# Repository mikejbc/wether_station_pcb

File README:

# Schemat Stacji Pogodowej wraz z projektem płytki PCB

Cechy projektu:

+ Oparty na mikrokontrolerze Atmega328
+ Wykorzystuje Czujnik temperatury i wilgotności DHT 22
+ ...

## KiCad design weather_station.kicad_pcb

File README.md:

# Schemat Stacji Pogodowej wraz z projektem płytki PCB

Cechy projektu:

+ Wykonany w Kicad
+ Oparty na mikrokontrolerze Atmega328
+ Wykorzystuje Czujnik temperatury i wilgotności DHT 22
+ ...

## Źródła:

+ https://howtomechatronics.com/tutorials/arduino/arduino-wireless-weather-station-project/

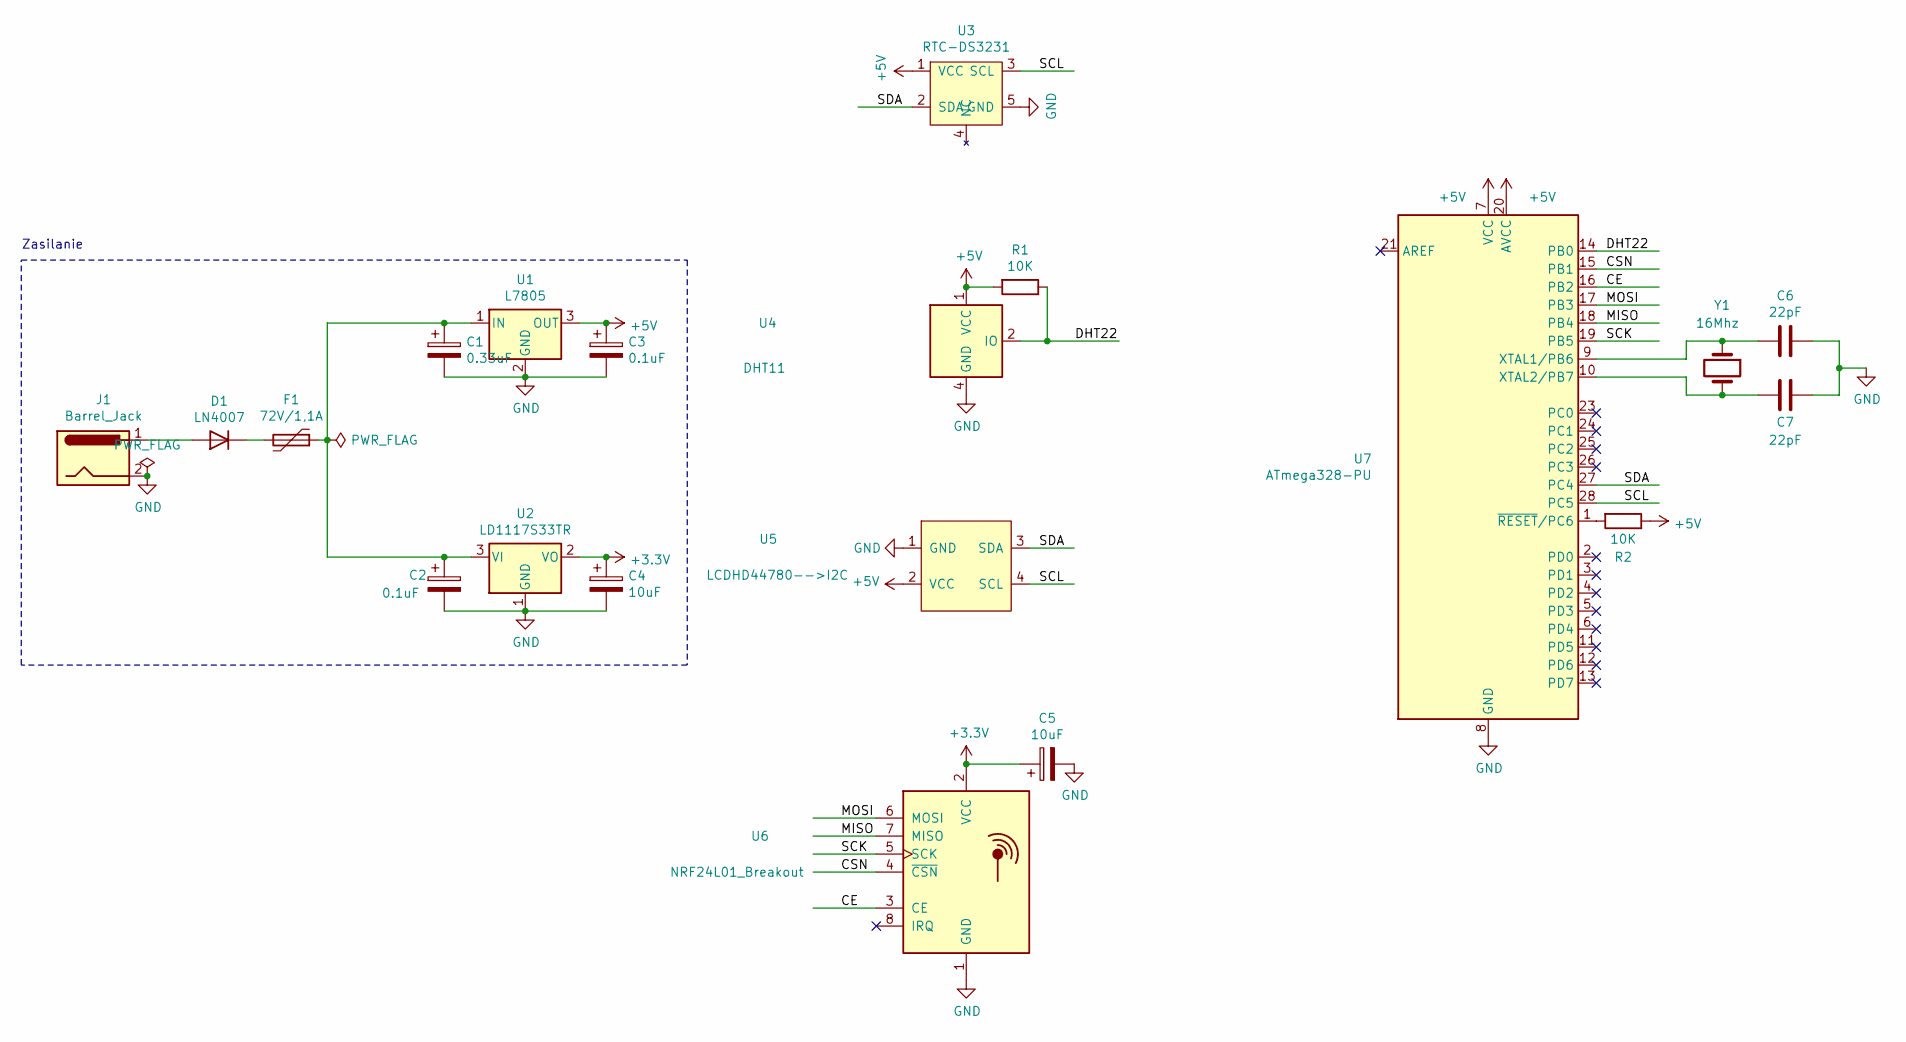
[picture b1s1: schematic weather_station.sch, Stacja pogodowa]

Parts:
C1: 0.33uF; CP_Radial_D5.0mm_P2.00mm
C2, C3: 0.1uF; CP_Radial_D5.0mm_P2.00mm
C4, C5: 10uF; CP_Radial_D5.0mm_P2.00mm
C6, C7: 22pF; C_Disc_D3.0mm_W1.6mm_P2.50mm
D1: LN4007; D_DO-41_SOD81_P10.16mm_Horizontal
F1: 72V/1,1A; Fuse_BelFuse_0ZRE0016FF_L9.9mm_W3.8mm
J1: Barrel_Jack; BarrelJack_Horizontal
R1, R2: 10K; R_Axial_DIN0207_L6.3mm_D2.5mm_P10.16mm_Horizontal
U1: L7805; TO-220-3_Vertical
U2: LD1117S33TR; TO-220-3_Vertical
U3: RTC-DS3231; PinHeader_1x05_P2.54mm_Vertical
U4: DHT11; Aosong_DHT11_5.5x12.0_P2.54mm
U5: LCDHD44780-->I2C; PinHeader_1x04_P2.54mm_Vertical
U6: NRF24L01_Breakout; NRF24-horizontal-pin-socket
U7: ATmega328-PU; DIP-28_W7.62mm_Socket
Y1: 16Mhz; Crystal_HC49-4H_Vertical

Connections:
+3V3: C4.1, C5.1, U2.2 (VO), U6.2 (VCC)
+5V: C3.1, R1.2, R2.1, U1.3 (OUT), U3.1 (VCC), U4.1 (VCC), U5.2 (VCC), U7.7 (VCC), U7.20 (AVCC)
/CE: U6.3 (CE), U7.16 (PB2)
/CSN: U6.4 (~CSN), U7.15 (PB1)
/DHT22: R1.1, U4.2 (IO), U7.14 (PB0)
/MISO: U6.7 (MISO), U7.18 (PB4)
/MOSI: U6.6 (MOSI), U7.17 (PB3)
/SCK: U6.5 (SCK), U7.19 (PB5)
/SCL: U3.3 (SCL), U5.4 (SCL), U7.28 (PC5)
/SDA: U3.2 (SDA), U5.3 (SDA), U7.27 (PC4)
GND: C1.2, C2.2, C3.2, C4.2, C5.2, C6.1, C7.1, J1.2, U1.2 (GND), U2.1 (GND), U3.5 (GND), U4.4 (GND), U5.1 (GND), U6.1 (GND), U7.8 (GND), U7.22 (GND)
unnamed: C1.1, C2.1, F1.1, U1.1 (IN), U2.3 (VI)
unnamed: C6.2, U7.9 (XTAL1/PB6), Y1.1
unnamed: C7.2, U7.10 (XTAL2/PB7), Y1.2
unnamed: D1.1 (K), F1.2
unnamed: D1.2 (A), J1.1
unnamed: R2.2, U7.1 (~RESET~/PC6)

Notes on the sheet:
Zasilanie

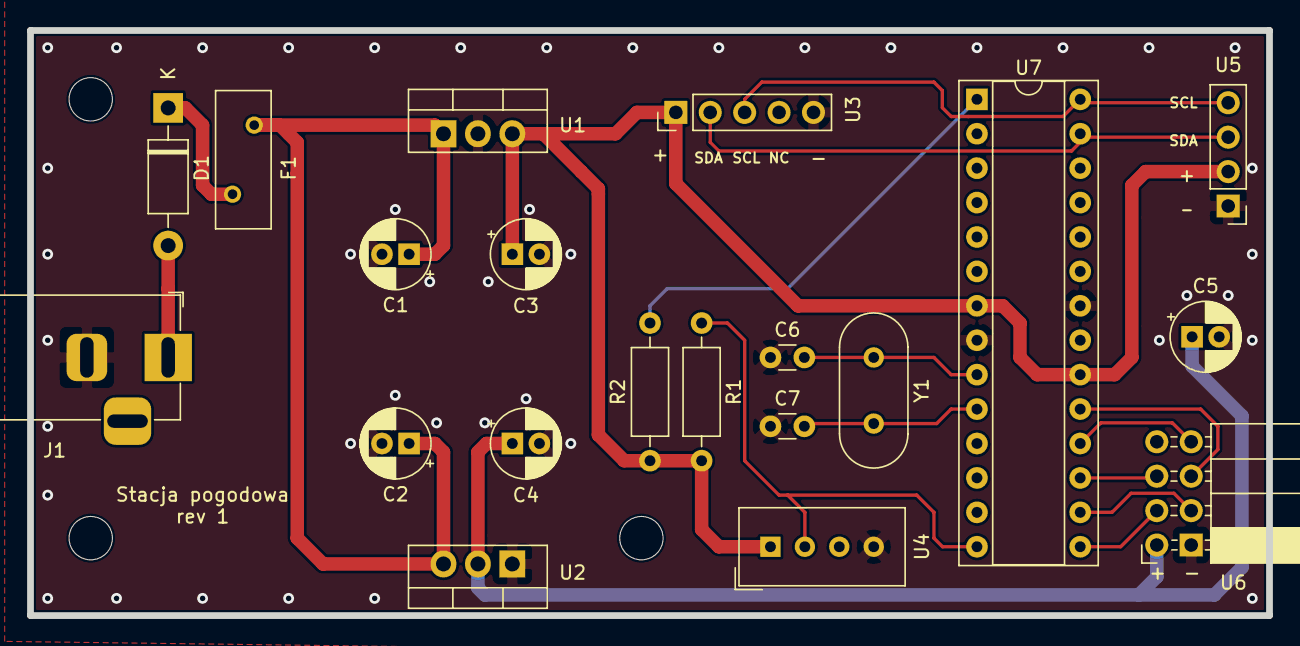
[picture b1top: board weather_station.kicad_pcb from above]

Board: 2 copper layers, 91.4 x 43.2 mm, 20 parts (0 on the bottom side), 17 nets.

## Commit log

2021-01-08 stacja pogodowa
2021-01-08 dodano opis
2021-01-08 opis w md
2021-01-08 Dodano zdjęcia schematów wykorzystanych do projektu
2021-01-08 Zdjęcie pcb w README
2021-01-08 źródła w rdm
2021-01-10 Poprawiona płytka (konektor NRF24 oraz otwory na śrubki)
2021-01-10 nowy render płytki
2021-01-10 Zmiana otworów na śruby z M2 na M3
2021-01-11 Wersja wysłana do produkcji
2021-01-15 schemat w pdf
2021-01-15 Create LICENSE
